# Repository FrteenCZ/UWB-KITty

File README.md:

# UWB-KITty
This project is designed to deliver high-precision indoor tracking using UWB technology, with a focus on usability and modularity.

## Features
- 🧭 Real-time trilateration using UWB anchors and tags
- 🐾 Accurate position estimation indoors
- 📡 Flexible architecture (ROS / custom middleware)
- 🛠️ Calibration tools and visualization

## 📂 Folder Structure

```

UWB-KITty/
├── docs/               # Diagrams, specifications, documentation
├── hardware/           # Schematics, anchor/tag configs
├── src/                # Core source code (localization, filtering, etc.)
├── sim/                # Simulation tools and configs
├── scripts/            # Helper scripts (e.g., setup, calibration)
├── tests/              # Unit tests and mock environments
├── README.md
└── LICENSE

````

## 🚀 Getting Started

```bash
git clone https://github.com/yourusername/UWB-KITty.git
cd UWB-KITty
# Installation / setup instructions
````

## 📜 Licenses and Acknowledgments

This project uses the [**DW1000 driver** by thotro](https://github.com/thotro/arduino-dw1000), licensed under the [Apache License 2.0](https://www.apache.org/licenses/LICENSE-2.0).

My own code is licensed under the MIT License.

Please refer to the respective LICENSE files for full terms.

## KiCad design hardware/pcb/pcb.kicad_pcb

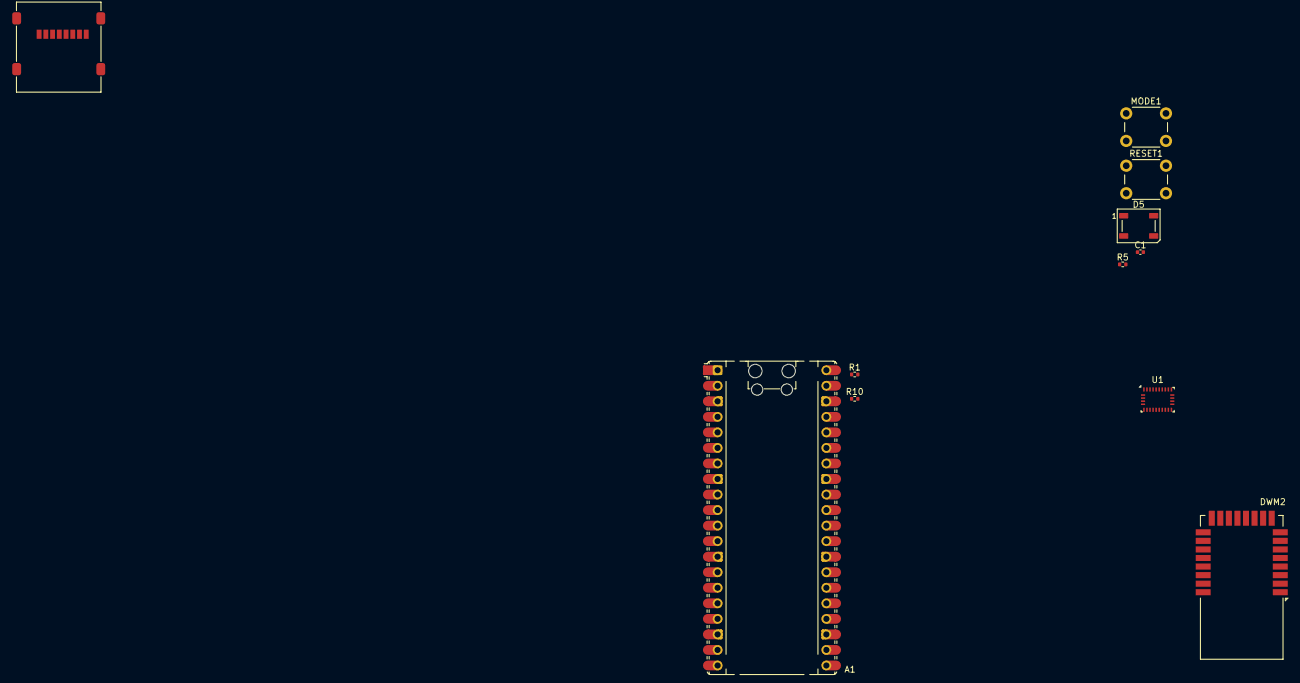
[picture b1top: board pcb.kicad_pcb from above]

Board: 2 copper layers, 11 parts (0 on the bottom side), 7 nets, no tracks yet.

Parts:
A1: RaspberryPi_Pico_W; RaspberryPi_Pico_Common_Unspecified
C1: 100nf; C_0402_1005Metric
D5: WS2812B; LED_WS2812B_PLCC4_5.0x5.0mm_P3.2mm
DWM2: DWM3000; DWM1000
J1: Micro_SD_Card; microSD_HC_Molex_47219-2001
MODE1: MODE; SW_PUSH_6mm
R1, R5: 10k; R_0402_1005Metric
R10: IDK; R_0402_1005Metric
RESET1: RESET; SW_PUSH_6mm
U1: BNO055; LGA-28_5.2x3.8mm_P0.5mm

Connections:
+3V3: R5.1, U1.3 (VDD), U1.28 (VDDIO)
/ENABLE: C1.1, R5.2, RESET1.2
/UWB-IRQ: DWM2.22 (IRQ/GPIO8), R1.1
GND: C1.2, D5.3 (VSS), DWM2.8 (VSS), DWM2.16 (VSS), DWM2.21 (VSS), DWM2.23 (VSS), DWM2.24 (VSS), J1.6 (VSS), J1.9 (SHIELD), MODE1.1, R1.2, R10.2, RESET1.1, U1.2 (GND), U1.5 (PS1), U1.6 (PS0), U1.18 (COM2), U1.25 (GNDIO)
unnamed: A1.3 (GND), A1.8 (GND), A1.13 (GND), A1.18 (GND), A1.23 (GND), A1.28 (GND), A1.38 (GND)
unnamed: DWM2.5 (VDDAON), DWM2.6 (VDD3V3), DWM2.7 (VDD3V3)
unnamed: DWM2.2 (WAKEUP), R10.1

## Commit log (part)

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2025-02-13 renamed file_system to main and moved all files a step up from locator to src
2025-02-15 rewrited main.cpp for better usage and readability
2025-02-15 seperated out LED_test to its own file
2025-02-15 quick fix
2025-02-16 web page for LED_test and wifi_connection added
2025-02-16 added scan wifi function into a utils
2025-02-16 fix the scan_wifi function
2025-02-17 added connect_to_wifi function + rewrited for better readability
2025-02-18 start_AP function for starting access piont
2025-02-19 wifi_connection mode
2025-02-22 added ability to send strings in LED_test
2025-02-22 fix: correct RSSI value handling in WiFi scanning
2025-02-25 new wifi connection website
2025-02-25 created main menu for website
2025-02-25 updated control menu
2025-02-25 feat: implement WiFi location matching functionality with similarity calculation
2025-02-26 better button animations
2025-02-26 renamed main.html to index.html
2025-03-05 feat: add UWB module with setup and loop functions for device ranging
2025-03-05 refactor: update platformio.ini to support multiple ESP32 environments with distinct upload and monitor ports and modes for UWB
2025-03-05 refactor: some minor changes docs: add comments to the code
2025-03-05 feat: implement Wi-Fi connection handling with dynamic network fetching
2025-03-06 feat: implement location handling with HTTP endpoints for Wi-Fi scanning and matching
2025-03-06 chore: remove unused include and lib directories
2025-03-06 refactor: update JSON handling in Wi-Fi location module and adjust route definitions
2025-03-06 refactor: simplify JSON handling for Wi-Fi credentials in connection logic
2025-03-28 separate css file
2025-04-17 feat: UWB finally works, meassures distances, runtime mode switch
2025-04-17 fix: swap UWB_PIN_SPI_IRQ and UWB_PIN_SPI_RST definitions for correct pin mapping
2025-04-17 docs: add comments to the UWB functions
2025-04-17 feat: add UWB Control Panel HTML interface for managing ranging and mode switching
2025-04-17 feat: enhance UWB functionality with web server endpoints for ranging control and status
2025-04-17 feat: add HTML endpoints for LED test, Wi-Fi connection, and location handling
2025-04-18 feat: implement averaging for distance measurements in UWB module
2025-04-18 feat: add UWB calibration functionality
2025-04-18 feat: add calibration feature to UWB Control Panel HTML interface
2025-04-18 fix: correct password key in Wi-Fi credential handling
2025-04-18 refactor: renamed place.html to location.html
2025-04-18 fix: adjust delay parameters and improve calibration logging in UWB module
2025-04-20 fixed index
2025-04-20 actually fixed index
2025-04-20 add css to UWB website
2025-04-21 feat: implement preferences for antenna delay and ranging state management
2025-04-22 tweak
2025-04-30 fix: update window.onload to fetch WiFi networks instead of rendering fixed list
2025-04-30 refactor: reorganize code structure and enhance WiFi handling with new routing and error handling
2025-04-30 feat: add credential configuration file for WiFi SSID and password example
2025-04-30 feat: implement serial input handling
2025-04-30 feat: add UWB start and stop functions, rename switchMode for clarity
2025-04-30 feat: moved the trilateration logic into the main project
2025-04-30 fix: fixed UWB functions to their new names and reduce redundancy
2025-06-22 Rename LICENSE to LICENSE MIT.md
2025-06-22 Create LICENSE
2025-06-22 renamed Apache LICENSE
2025-06-22 Add .gitignore to exclude __pycache__ directory
2025-06-22 Add initial implementation of UWB-KITty object tracking feature
2025-06-23 Refactor object tracking feature: separate draw logic and operator into distinct modules
2025-07-01 Add distance drawing feature and UI panel for distance display
2025-07-01 Add trilateration enviroment
2025-07-02 feat: enabled inputing multiple points at the same times and deleted uneccessary Serial prints
2025-07-04 Add communication module and integrate ESP communication functionality
2025-07-04 feat: add printJSON method to output matrix in JSON format
2025-07-04 feat: add JSON output for trilateration solution and Kalman filter state
2025-07-04 enhance parsing json from ESP
2025-07-19 fix: PCA algorithm now works and is separeted into two functions
2025-07-20 feat: enhance eigenJacobi method to sort eigenvalues and eigenvectors by absolute value
2025-07-21 Refactor tracking panel to handle object selection and improve user feedback
2025-07-21 feat: enhance dimensional reduction for more robust solution
2025-08-28 moved the code for ESP to its own folder
2025-09-02 feat: find the corection distance in undetermined systems
2025-09-02 now it just like work (somehow), I ll make it better later
2025-09-06 refactor: send the whole state in one JSON
2025-09-07 feat: enhance ESP comunicationand scene update
2025-09-07 feat: enhance scene update to visualize solution space in undetermined cases
2025-09-08 feat: improve ensure_empty function to manage collection linking and unlinking
2025-09-11 feat: add automatic detection of serial devices for ESP connection
2025-09-12 feat: update serial device detection to use pyserial for improved compatibility
2025-09-12 feat: enhance trilateration algorithm to handle edge cases and improve state reporting
2025-09-12 feat: improve device port user interface
2025-09-13 feat: add stop functionality for ESP serial connection in UI panel
2025-09-14 feat: major cleanup
2025-09-14 fix: fixed kalman filter
2025-09-18 feat: kalman filter now deals with null_space to find the most correct solution according to the prediction
2025-11-03 PCB: begining of chematic and PCB layout
2025-11-06 PCB: progress on schematic
2025-11-09 finished schematic and routed pcb
2025-12-02 PCB progress
2025-12-09 added LCSC parts ids for assembly
2025-12-13 I dont remeber, something with PCB :)
2025-12-14 add neeko
2025-12-15 reroute dálnice for backlit lightbulb
2025-12-19 PCB: add some silkscreen art and transparency edits
2025-12-26 PCB: modified LCSC part numbers for D5 and J3
2026-01-06 Added that small bitchass resistor that was missing. (For those who come after)
2026-01-09 Update platformio.ini and config.h for new board configuration
2026-01-09 Add StatusLED functionality with color control
2026-01-10 Implement VirtualDevice class with setAnchor and update methods (WIP)
2026-01-10 Refactor serial control: streamline command handling
2026-01-10 Refactor serial control: remove virtual device and dynamic dymensionality variables and commands
2026-01-10 The ranging is running, its is just not correct :,)
2026-01-11 Add button handling functionality with setup and update methods
2026-01-18 Refactor UWB module: remove unused calibration code and streamline ranging setup
2026-01-20 Refactor SerialThread class: streamline initialization and improve command handling
2026-01-20 Add objectProperties module: implement UWB device properties and role visualization
2026-01-20 Refactor serial control operators: implement start and stop functionality for ESP communication
2026-01-20 Add communication protocol and command handling: implement distances calculation and trilateration command
2026-01-20 Add device and manager modules: implement Device class and command manager for handling device communication
2026-01-21 Refactor communication protocol: remove old parsing and distance calculation code, implement new Message and Protocol classes for better message handling
2026-02-05 Refactor communication protocol and device management: enhance message encoding/decoding, improve error handling, and implement visualizer for device states
2026-02-05 Add Blender utility functions: implement cleanup_collection, ensure_arrow, and ensure_empty for object management
2026-02-06 Implement the properties of devices saving to .blend file for better user expirinece
2026-02-06 Only allow tags to vizualize empties, remove debug prints
2026-02-06 Implemented a way to change the settings of a device
2026-02-07 Remove the unecessary # type: ignore, becuase I installed fake-bpy-module and there are no more warnings
2026-02-07 Fixed the start and stop simulation button
2026-02-08 Add VirtualMachine and VMManager classes for managing virtual machines and processing measurements
2026-02-09 Remove old virtual device files
2026-02-13 Change the type of device id from string to int
2026-02-14 Implemented command alias and silent prefix:"-" that prevents echo
2026-02-20 Refactor command response handling to use helper functions for improved readability and consistency
2026-02-20 Add initial Serial Communication Protocol documentation
2026-03-06 Added tag id to the trilateration response
2026-03-06 Enhanced the comunication
2026-03-24 DWM3000 schematic done
2026-03-27 Added IMU
2026-04-09 progress :)
2026-04-09 push now test later math
